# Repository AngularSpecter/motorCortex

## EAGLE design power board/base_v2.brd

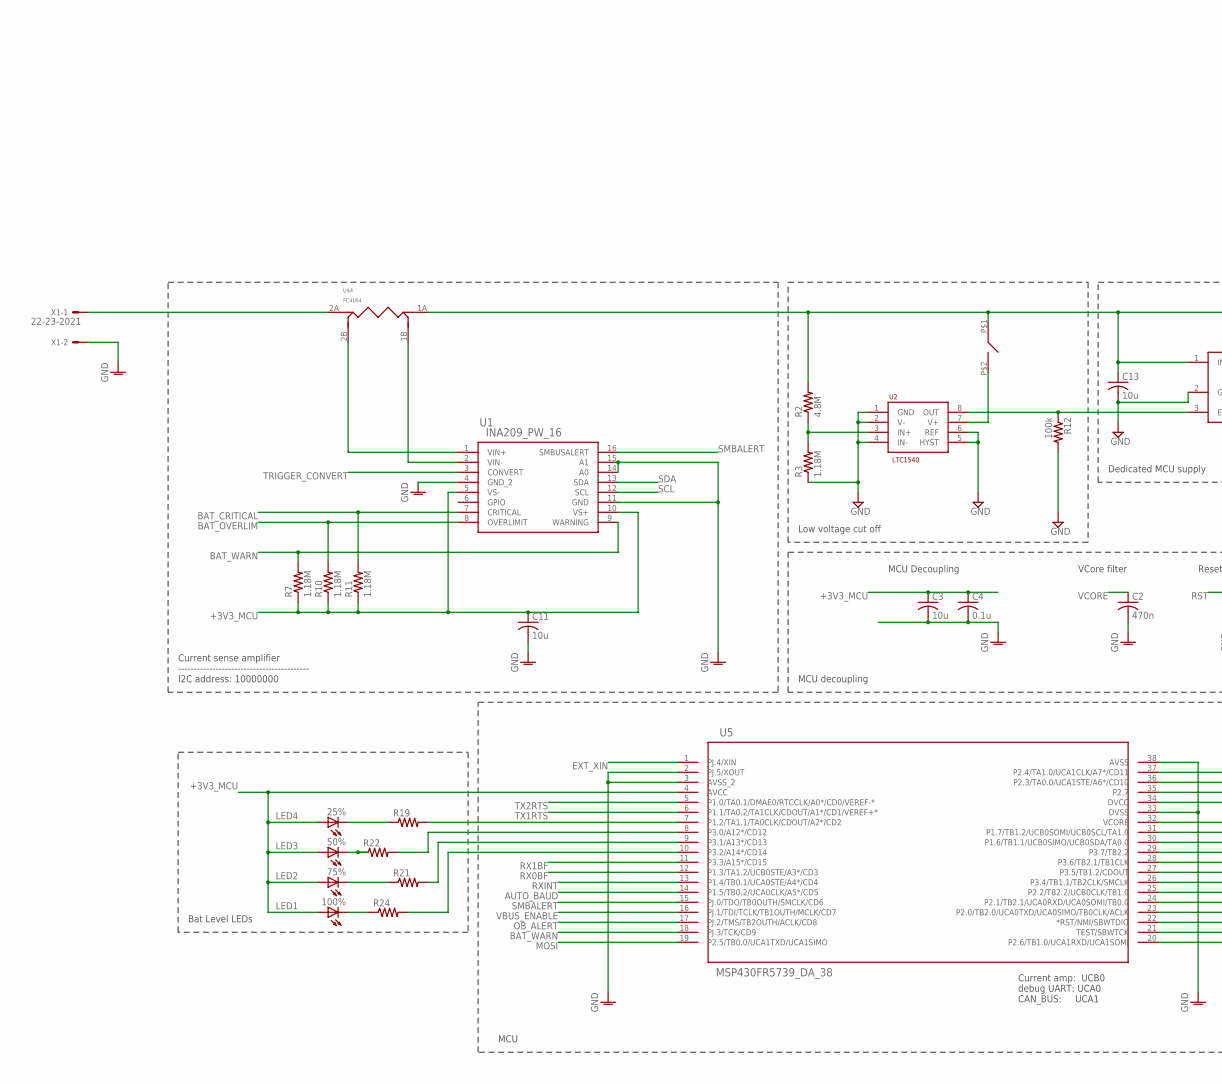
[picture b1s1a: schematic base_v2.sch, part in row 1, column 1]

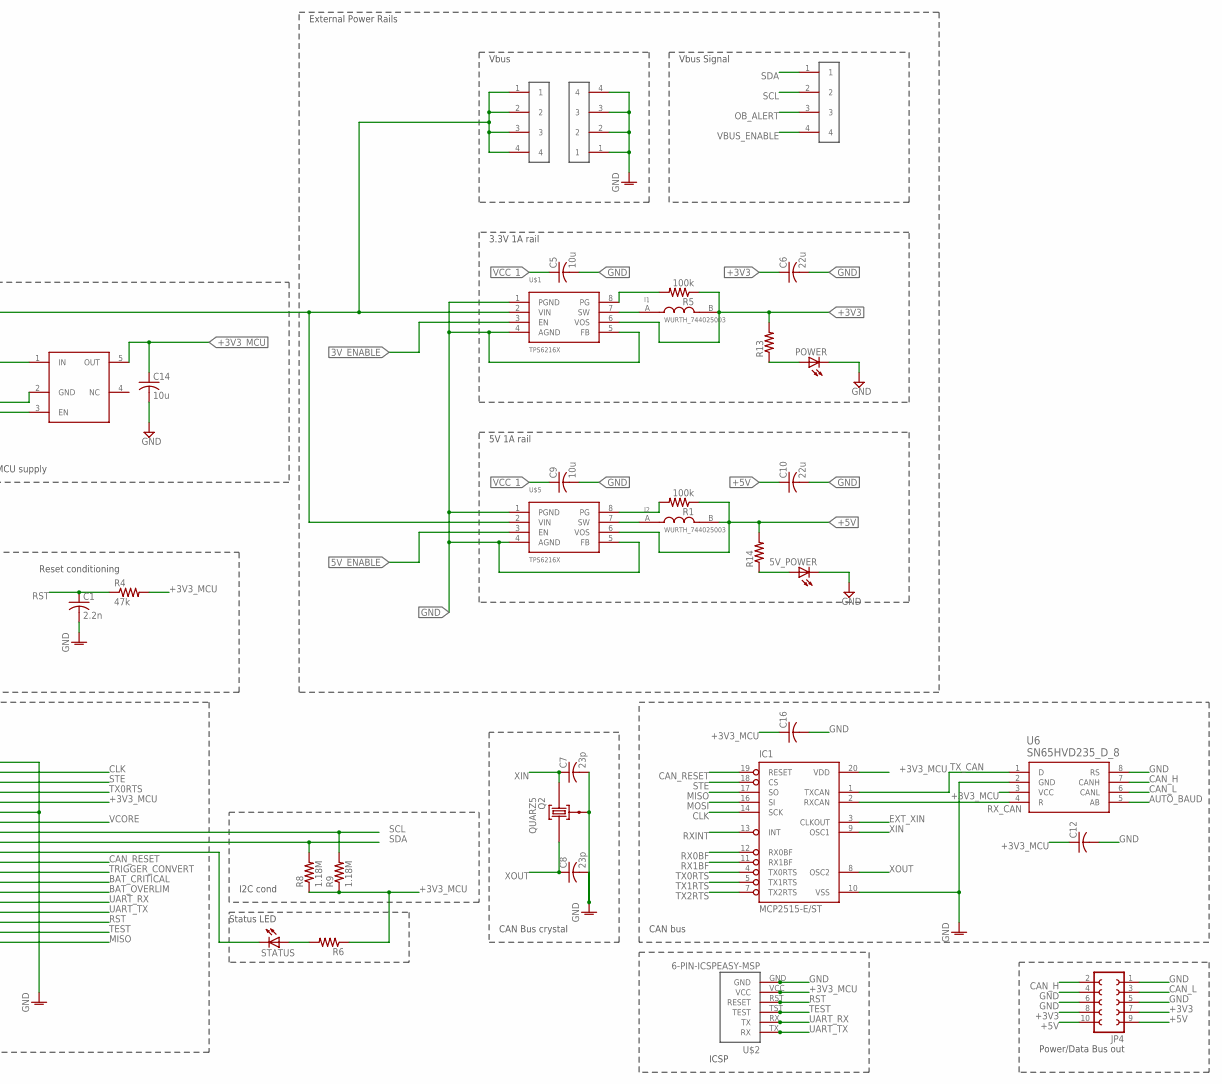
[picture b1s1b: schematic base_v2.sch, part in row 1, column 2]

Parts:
5V_POWER, 25%, 50%, 75%, 100%: LEDCHIP-LED0603; CHIP-LED0603
C1: 2.2n; C1206
C2: 470n; C1206
C3, C5, C9, C11, C13, C14: 10u; C1206
C4: 0.1u; C1206
C6, C10: 22u; C1206
C7, C8: 23p; C1206
C12, C16: C-USC0603; C0603
I1, I2: WURTH_744025003; INDUCTOR
IC1: MCP2515-E/ST; TSSOP20
JP4: FE05-2
POWER: LEDCHIP-LED0603; CHIP-LED0603
Q2: QUARZ5
R1, R5, R12: 100k; R1206
R2: 4.8M; R1206
R3: 1.18M; R1206
R4: 47k; R1206
R6, R13, R14, R19, R21, R22, R24: R-US_R0603; R0603
R7, R8, R9, R10, R11: 1.18M; R0805
STATUS: LEDCHIP-LED0603; CHIP-LED0603
U1: INA209_PW_16; PW16
U2: LTC1540; S8
U5: MSP430FR5739_DA_38; DA38
U6: SN65HVD235_D_8; D8
U$1, U$5: TPS6216X; DGK-8(VSSOP)
U$2: 6-PIN-ICSPEASY-MSP; EASYMSP-6PIN
U$3, U$8, U$11: 1X4_HEADER; 1X4-.1HEADER
U$4: FC4L64
U$6: TPS70930-Q1; SOT-23
U$7: A6SN; DIP1-SMT
X1: 22-23-2021

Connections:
3V_ENABLE: U$1.3 (EN)
5V_ENABLE: U$5.3 (EN)
+3V3: C6.1, I1.B, JP4.7, JP4.8, R5.1, R13.2, U$1.6 (VOS)
+3V3_MCU: 25%.A, 50%.A, 75%.A, 100%.A, C3.1, C4.1, C11.1, C12.1, C14.1, C16.1, IC1.20 (VDD), R4.2, R6.1, R7.1, R8.1, R9.1, R10.1, R11.1, U1.5 (VS-), U1.10 (VS+), U5.4 (AVCC), U5.34 (DVCC), U6.3 (VCC), U$2.VCC, U$6.5 (OUT)
+5V: C10.1, I2.B, JP4.9, JP4.10, R1.1, R14.2, U$5.6 (VOS)
AUTO_BAUD: U5.14 (P1.5/TB0.2/UCA0CLK/A5*/CD5), U6.5 (AB)
BAT_CRITICAL: R11.2, U1.7 (CRITICAL), U5.26 (P3.4/TB1.1/TB2CLK/SMCLK)
BAT_OVERLIM: R10.2, U1.8 (OVERLIMIT), U5.25 (P2.2/TB2.2/UCB0CLK/TB1.0)
BAT_WARN: R7.2, U1.9 (WARNING), U5.18 (PJ.3/TCK/CD9)
CAN_H: JP4.2, U6.7 (CANH)
CAN_L: JP4.3, U6.6 (CANL)
CAN_RESET: IC1.19 (RESET), U5.28 (P3.6/TB2.1/TB1CLK)
CLK: IC1.14 (SCK), U5.37 (P2.4/TA1.0/UCA1CLK/A7*/CD11)
EXT_XIN: IC1.3 (CLKOUT), U5.1 (PJ.4/XIN)
GND: 5V_POWER.C, C1.2, C2.2, C3.2, C4.2, C5.2, C6.2, C7.2, C8.2, C9.2, C10.2, C11.2, C12.2, C13.2, C14.2, C16.2, IC1.10 (VSS), JP4.1, JP4.4, JP4.5, JP4.6, POWER.C, Q2.GND@0 (0), R3.1, R12.2, U1.4 (GND_2), U1.11 (GND), U1.14 (A0), U1.15 (A1), U2.1 (GND), U2.2 (V-), U2.4 (IN-), U2.5 (HYST), U2.6 (REF), U5.2 (PJ.5/XOUT), U5.3 (AVSS_2), U5.33 (DVSS), U5.38 (AVSS), U6.2 (GND), U6.8 (RS), U$1.1 (PGND), U$1.4 (AGND), U$1.5 (FB), U$2.GND, U$3.1, U$3.2, U$3.3, U$3.4, U$5.1 (PGND), U$5.4 (AGND), U$5.5 (FB), U$6.2 (GND), X1.2
LED1: R24.2, U5.10 (P3.2/A14*/CD14)
LED2: R21.2, U5.9 (P3.1/A13*/CD13)
LED3: R22.2, U5.8 (P3.0/A12*/CD12)
LED4: R19.2, U5.7 (P1.2/TA1.1/TA0CLK/CDOUT/A2*/CD2)
MISO: IC1.17 (SO), U5.20 (P2.6/TB1.0/UCA1RXD/UCA1SOMI)
MOSI: IC1.16 (SI), U5.19 (P2.5/TB0.0/UCA1TXD/UCA1SIMO)
unnamed: 25%.C, R19.1
unnamed: U2.7 (V+), U$7.P$2 (2)
unnamed: R2.1, R3.2, U2.3 (IN+)
unnamed: I1.A, U$1.7 (SW)
unnamed: I2.A, U$5.7 (SW)
unnamed: R5.2, U$1.8 (PG)
unnamed: R1.2, U$5.8 (PG)
unnamed: U$4.2A (1A), X1.1
unnamed: POWER.A, R13.1
unnamed: 5V_POWER.A, R14.1
unnamed: U1.1 (VIN+), U$4.2B (1B)
unnamed: U1.2 (VIN-), U$4.1B (2B)
unnamed: R6.2, STATUS.A
unnamed: 50%.C, R22.1
unnamed: 75%.C, R21.1
unnamed: 100%.C, R24.1
NC: STATUS.C, U5.29 (P3.7/TB2.2)
OB_ALERT: U5.17 (PJ.2/TMS/TB2OUTH/ACLK/CD8), U$8.3
RST: C1.1, R4.1, U5.22 (*RST/NMI/SBWTDIO), U$2.RST (RESET)
RX0BF: IC1.12 (RX0BF), U5.12 (P1.3/TA1.2/UCB0STE/A3*/CD3)
RX1BF: IC1.11 (RX1BF), U5.11 (P3.3/A15*/CD15)
RXINT: IC1.13 (INT), U5.13 (P1.4/TB0.1/UCA0STE/A4*/CD4)
RX_CAN: IC1.2 (RXCAN), U6.4 (R)
SCL: R9.2, U1.12 (SCL), U5.31 (P1.7/TB1.2/UCB0SOMI/UCB0SCL/TA1.0), U$8.2
SDA: R8.2, U1.13 (SDA), U5.30 (P1.6/TB1.1/UCB0SIMO/UCB0SDA/TA0.0), U$8.1
SMBALERT: U1.16 (SMBUSALERT), U5.15 (PJ.0/TDO/TB0OUTH/SMCLK/CD6)
STE: IC1.18 (CS), U5.36 (P2.3/TA0.0/UCA1STE/A6*/CD10)
TEST: U5.21 (TEST/SBWTCK), U$2.TST (TEST)
TRIGGER_CONVERT: U1.3 (CONVERT), U5.27 (P3.5/TB1.2/CDOUT)
TX0RTS: IC1.4 (TX0RTS), U5.35 (P2.7)
TX1RTS: IC1.5 (TX1RTS), U5.6 (P1.1/TA0.2/TA1CLK/CDOUT/A1*/CD1/VEREF+*)
TX2RTS: IC1.7 (TX2RTS), U5.5 (P1.0/TA0.1/DMAE0/RTCCLK/A0*/CD0/VEREF-*)
TX_CAN: IC1.1 (TXCAN), U6.1 (D)
UART_RX: U5.24 (P2.1/TB2.1/UCA0RXD/UCA0SOMI/TB0.0), U$2.RX (TX)
UART_TX: U5.23 (P2.0/TB2.0/UCA0TXD/UCA0SIMO/TB0CLK/ACLK), U$2.TX (RX)
VBUS_ENABLE: U5.16 (PJ.1/TDI/TCLK/TB1OUTH/MCLK/CD7), U$8.4
VCC_1: C5.1, C9.1, C13.1, R2.2, U$1.2 (VIN), U$4.1A (2A), U$5.2 (VIN), U$6.1 (IN), U$7.P$1 (1), U$11.1, U$11.2, U$11.3, U$11.4
VCORE: C2.1, U5.32 (VCORE)
VENABLE: R12.1, U2.8 (OUT), U$6.3 (EN)
XIN: C7.1, IC1.9 (OSC1), Q2.2
XOUT: C8.1, IC1.8 (OSC2), Q2.1

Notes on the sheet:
MCU Decoupling
Reset conditioning
VCore filter
Current amp: UCB0 debug UART: UCA0 CAN_BUS: UCA1
3.3V 1A rail
5V 1A rail
Vbus
Current sense amplifier ------------------------------------------ I2C address: 10000000
Low voltage cut off
Dedicated MCU supply
Vbus Signal
External Power Rails
Bat Level LEDs
MCU decoupling
MCU
I2C cond
Status LED
CAN bus
CAN Bus crystal
ICSP
Power/Data Bus out

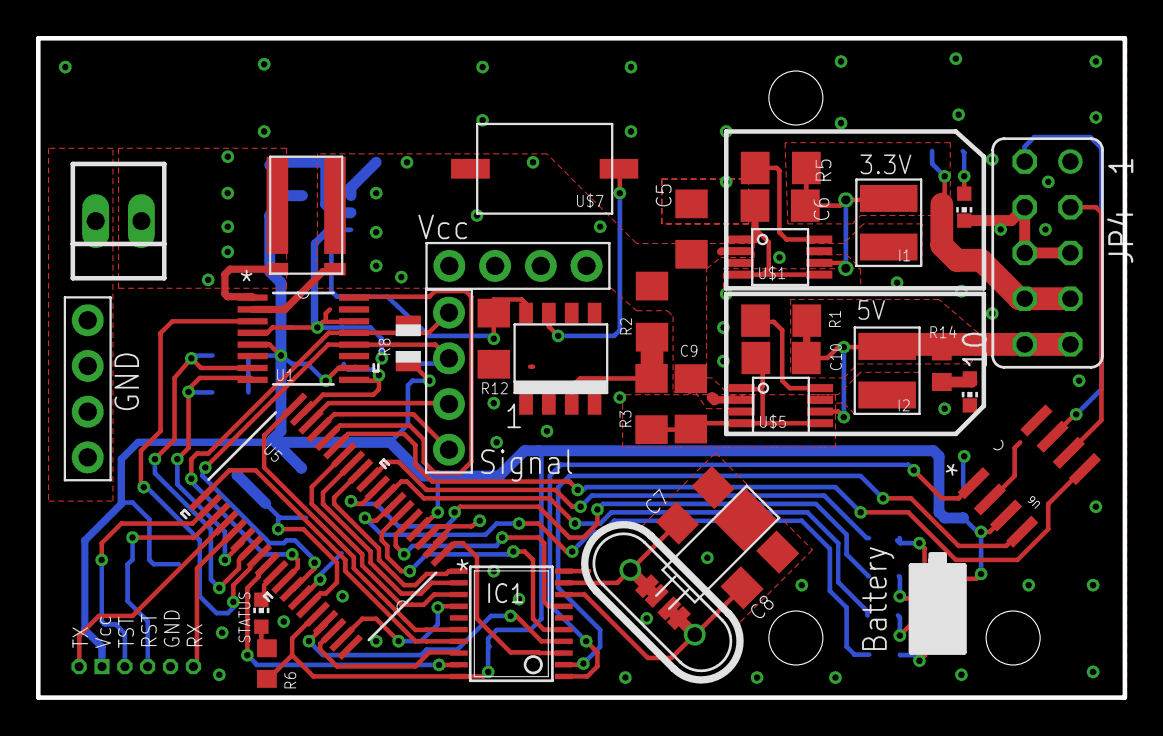
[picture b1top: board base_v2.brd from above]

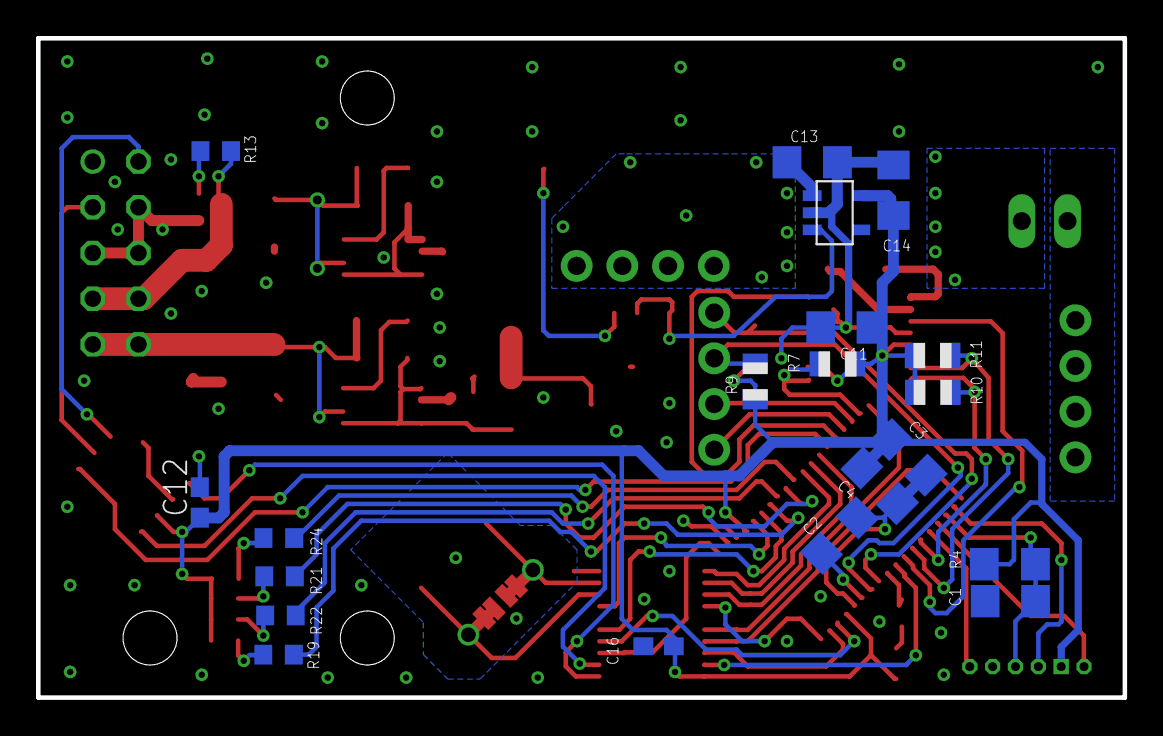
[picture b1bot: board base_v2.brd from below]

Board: 2 copper layers, 60.4 x 36.6 mm, 59 parts (20 on the bottom side), 60 nets.

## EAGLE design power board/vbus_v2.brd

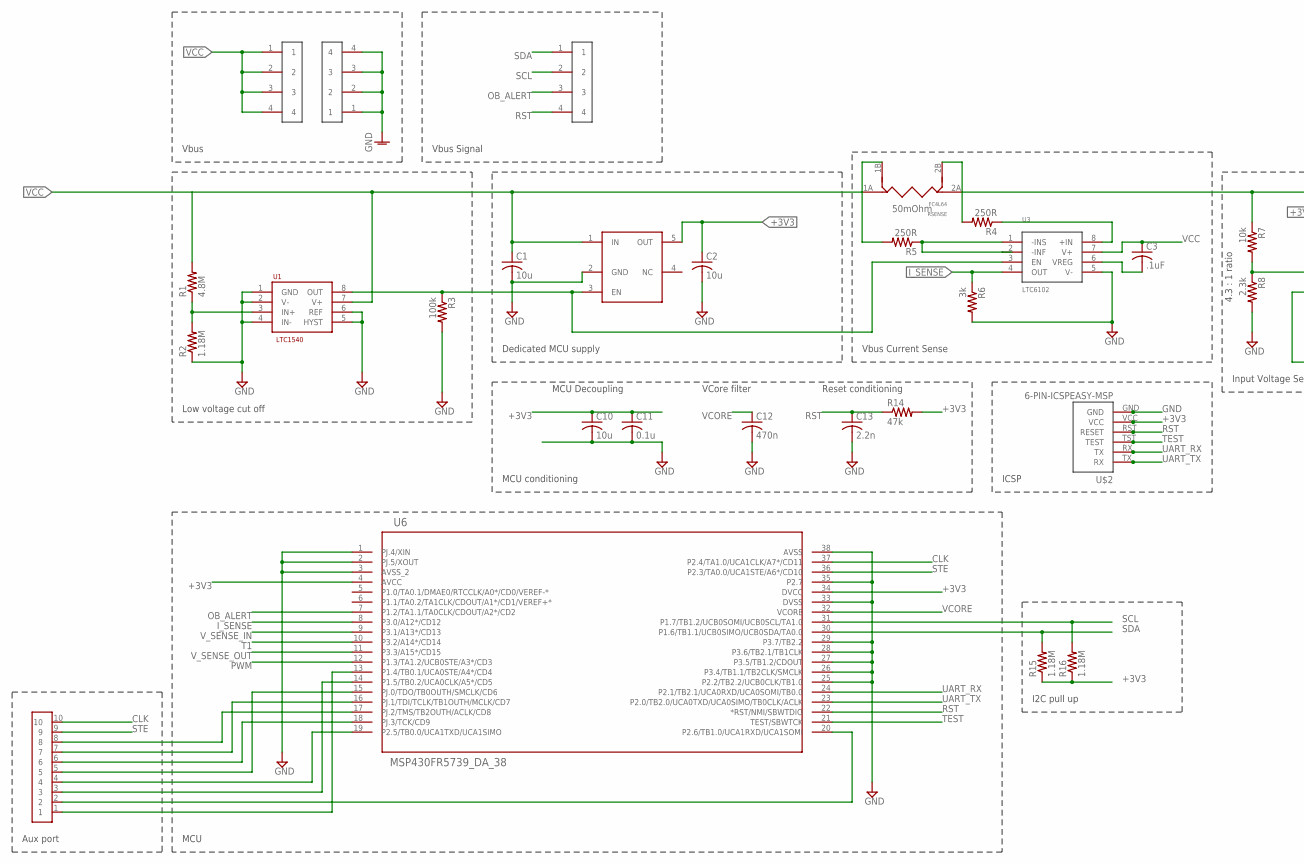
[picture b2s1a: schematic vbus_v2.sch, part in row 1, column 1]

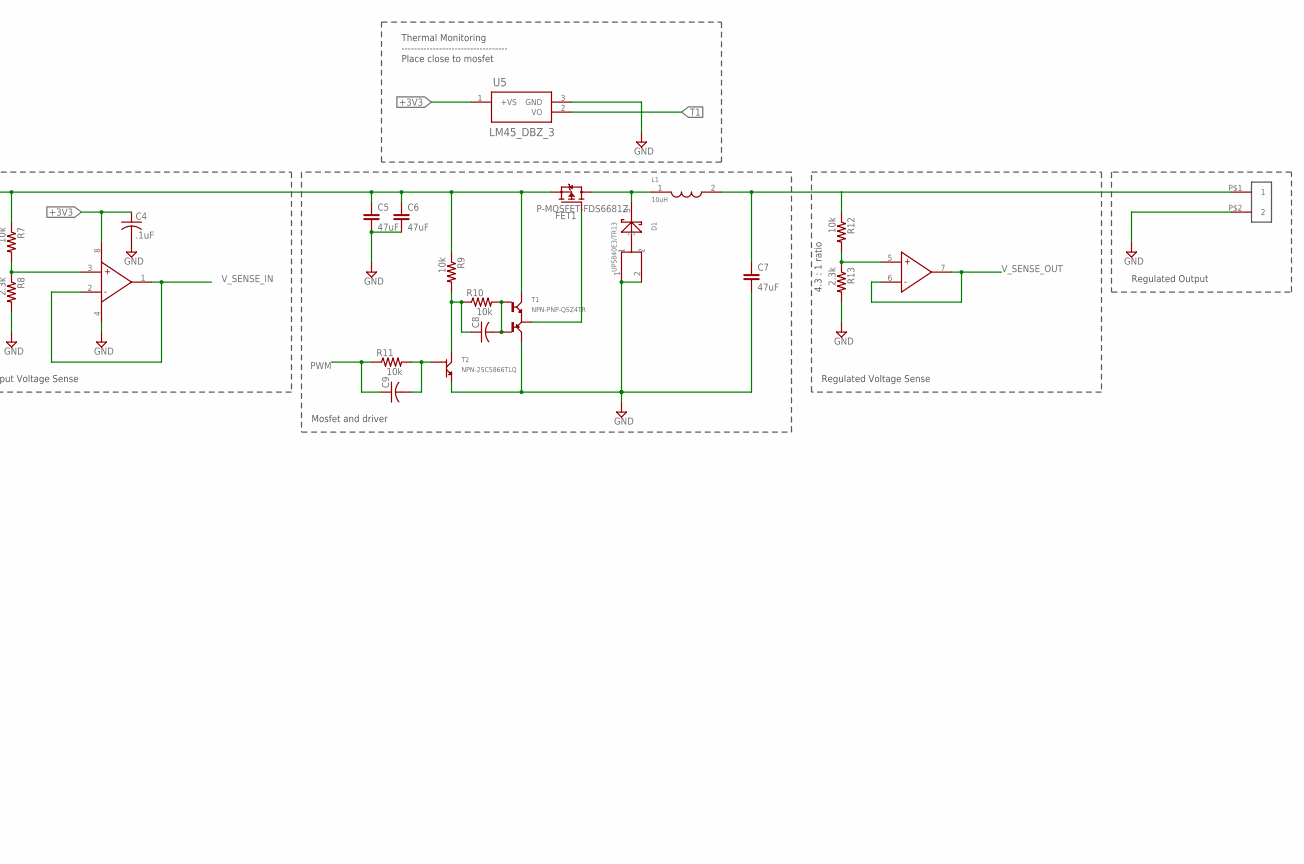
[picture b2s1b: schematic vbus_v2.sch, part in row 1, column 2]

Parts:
C1, C2, C10: 10u; C1206
C3, C4: .1uF; C0805
C5, C6, C7: 47uF; C1206
C8, C9: C-USC0805; C0805
C11: 0.1u; C1206
C12: 470n; C1206
C13: 2.2n; C1206
D1: UPS840E3/TR13; UPS840E3
FET1: P-MOSFET-FDS6681Z; SOIC-8
L1: 10uH; HCF1007
R1: 4.8M; R1206
R2: 1.18M; R1206
R3: 100k; R1206
R4, R5: 250R; M0805
R6: 3k; M0805
R7, R9, R10, R11, R12: 10k; M0805
R8, R13: 2.3k; M0805
R14: 47k; R1206
R15, R16: 1.18M; R0805
RSENSE: FC4L64
T1: NPN-PNP-QSZ4TR; TSMT5
T2: NPN-2SC5866TLQ; TSMT3
U1: LTC1540; S8
U2: TPS70930-Q1; SOT-23
U3: LTC6102; MS8
U4: LMP2202; D8-L
U5: LM45_DBZ_3; MF03A
U6: MSP430FR5739_DA_38; DA38
U$1: MICROPITCH; 2X5-1.27MM
U$2: 6-PIN-ICSPEASY-MSP; EASYMSP-6PIN
U$3, U$8, U$11: 1X4_HEADER; 1X4-.1HEADER
U$5: MOLEX-0436500200; MOLEX_MICROFIT-2

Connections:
+3V3: C2.1, C4.1, C10.1, C11.1, R14.2, R15.1, R16.1, U2.5 (OUT), U4.8 (VIN), U5.1 (+VS), U6.4 (AVCC), U6.34 (DVCC), U$2.VCC
CLK: U6.37 (P2.4/TA1.0/UCA1CLK/A7*/CD11), U$1.10
GND: C1.2, C2.2, C4.2, C5.2, C6.2, C7.2, C10.2, C11.2, C12.2, C13.2, D1.1, D1.2, R2.1, R3.2, R6.2, R8.2, R13.2, T1.5 (E), T2.2 (E), U1.1 (GND), U1.2 (V-), U1.4 (IN-), U1.5 (HYST), U1.6 (REF), U2.2 (GND), U3.5 (V-), U4.4 (GND), U5.3 (GND), U6.1 (PJ.4/XIN), U6.2 (PJ.5/XOUT), U6.3 (AVSS_2), U6.25 (P2.2/TB2.2/UCB0CLK/TB1.0), U6.26 (P3.4/TB1.1/TB2CLK/SMCLK), U6.27 (P3.5/TB1.2/CDOUT), U6.28 (P3.6/TB2.1/TB1CLK), U6.29 (P3.7/TB2.2), U6.33 (DVSS), U6.35 (P2.7), U6.38 (AVSS), U$2.GND, U$3.1, U$3.2, U$3.3, U$3.4, U$5.P$2 (2)
I_SENSE: R6.1, U3.4 (OUT), U6.8 (P3.0/A12*/CD12)
unnamed: R5.2, RSENSE.1B (2B)
unnamed: R1.1, R2.2, U1.3 (IN+)
unnamed: R4.1, U3.8 (+IN)
unnamed: R5.1, U3.1 (-INS), U3.2 (-INF)
unnamed: R4.2, RSENSE.2B (1B)
unnamed: C8.2, R10.2, T1.1 (G2), T1.3 (G1)
unnamed: C3.2, U3.6 (VREG)
unnamed: D1.3, FET1.1 (S), FET1.2 (S), FET1.3 (S), L1.1 (A)
unnamed: C8.1, R9.2, R10.1, T2.3 (C)
unnamed: C9.2, R11.2, T2.1 (B)
unnamed: U6.19 (P2.5/TB0.0/UCA1TXD/UCA1SIMO), U$1.4
unnamed: FET1.4 (G), T1.2 (G)
unnamed: U6.17 (PJ.2/TMS/TB2OUTH/ACLK/CD8), U$1.8
unnamed: U6.16 (PJ.1/TDI/TCLK/TB1OUTH/MCLK/CD7), U$1.7
unnamed: C5.1, C6.1, FET1.5 (D), FET1.6 (D), FET1.7 (D), FET1.8 (D), R7.1, R9.1, RSENSE.2A (1A), T1.4 (C)
unnamed: U6.15 (PJ.0/TDO/TB0OUTH/SMCLK/CD6), U$1.5
unnamed: U6.14 (P1.5/TB0.2/UCA0CLK/A5*/CD5), U$1.3
unnamed: U6.13 (P1.4/TB0.1/UCA0STE/A4*/CD4), U$1.1
unnamed: U6.18 (PJ.3/TCK/CD9), U$1.6
unnamed: U6.20 (P2.6/TB1.0/UCA1RXD/UCA1SOMI), U$1.2
OB_ALERT: U6.7 (P1.2/TA1.1/TA0CLK/CDOUT/A2*/CD2), U$8.3
PWM: C9.1, R11.1, U6.12 (P1.3/TA1.2/UCB0STE/A3*/CD3)
RST: C13.1, R14.1, U6.22 (*RST/NMI/SBWTDIO), U$2.RST (RESET), U$8.4
SCL: R16.2, U6.31 (P1.7/TB1.2/UCB0SOMI/UCB0SCL/TA1.0), U$8.2
SDA: R15.2, U6.30 (P1.6/TB1.1/UCB0SIMO/UCB0SDA/TA0.0), U$8.1
STE: U6.36 (P2.3/TA0.0/UCA1STE/A6*/CD10), U$1.9
T1: U5.2 (VO), U6.10 (P3.2/A14*/CD14)
TEST: U6.21 (TEST/SBWTCK), U$2.TST (TEST)
UART_RX: U6.24 (P2.1/TB2.1/UCA0RXD/UCA0SOMI/TB0.0), U$2.RX (TX)
UART_TX: U6.23 (P2.0/TB2.0/UCA0TXD/UCA0SIMO/TB0CLK/ACLK), U$2.TX (RX)
VCC: C1.1, C3.1, R1.2, RSENSE.1A (2A), U1.7 (V+), U2.1 (IN), U3.7 (V+), U$11.1, U$11.2, U$11.3, U$11.4
VCORE: C12.1, U6.32 (VCORE)
VENABLE: R3.1, U1.8 (OUT), U2.3 (EN), U3.3 (EN)
V_OUT: C7.1, L1.2 (B), R12.1, U$5.P$1 (1)
V_SENSE: R12.2, R13.1, U4.5 (+)
V_SENSE_IN: U4.1 (OUT), U4.2 (-), U6.9 (P3.1/A13*/CD13)
V_SENSE_IN_P: R7.2, R8.1, U4.3 (+)
V_SENSE_OUT: U4.6 (-), U4.7 (OUT), U6.11 (P3.3/A15*/CD15)

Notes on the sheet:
MCU Decoupling
Reset conditioning
VCore filter
Vbus
Low voltage cut off
Dedicated MCU supply
Vbus Signal
Thermal Monitoring ---------------------------------- Place close to mosfet
Regulated Voltage Sense
4.3 : 1 ratio
Vbus Current Sense
50mOhm
Input Voltage Sense
Mosfet and driver
Aux port
ICSP
MCU conditioning
I2C pull up
MCU
Regulated Output

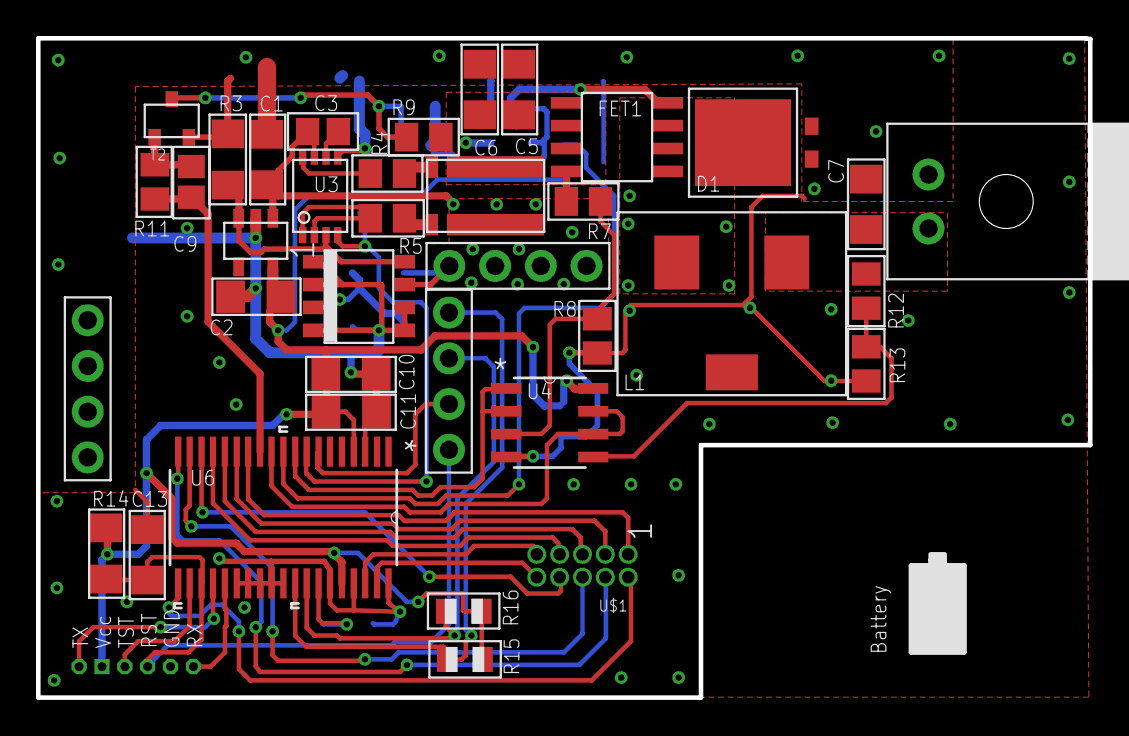
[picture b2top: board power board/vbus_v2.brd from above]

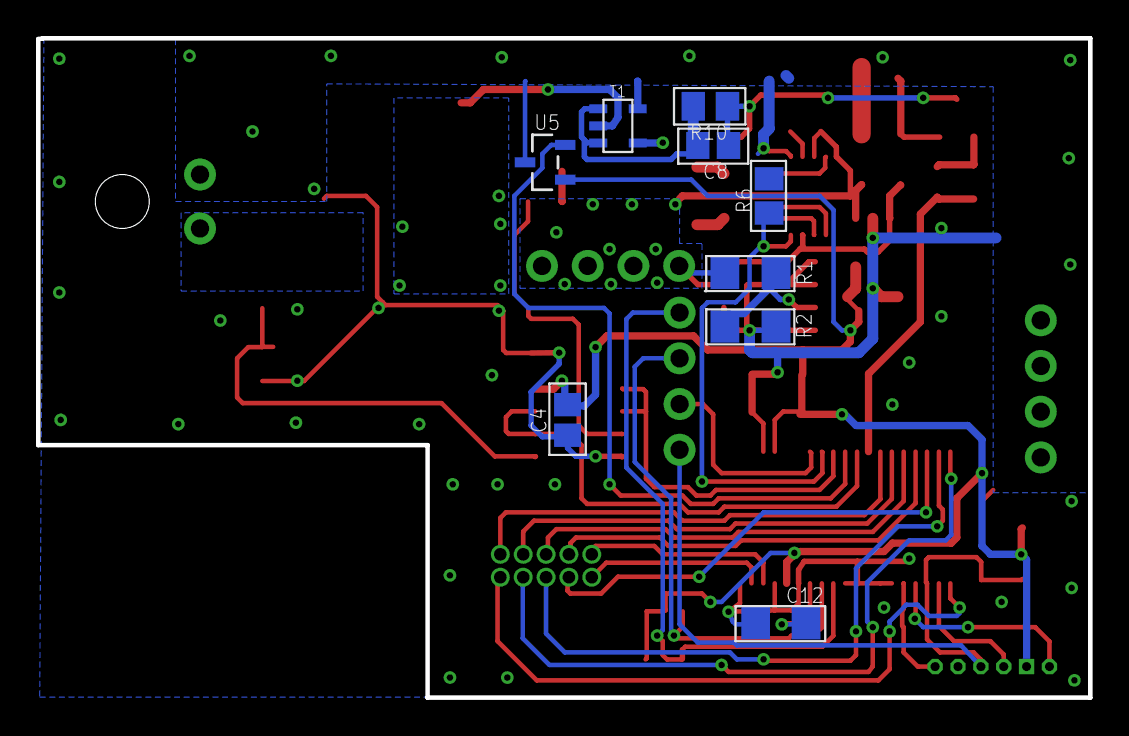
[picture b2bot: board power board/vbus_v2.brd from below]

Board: 2 copper layers, 58.4 x 36.6 mm, 47 parts (9 on the bottom side), 42 nets.

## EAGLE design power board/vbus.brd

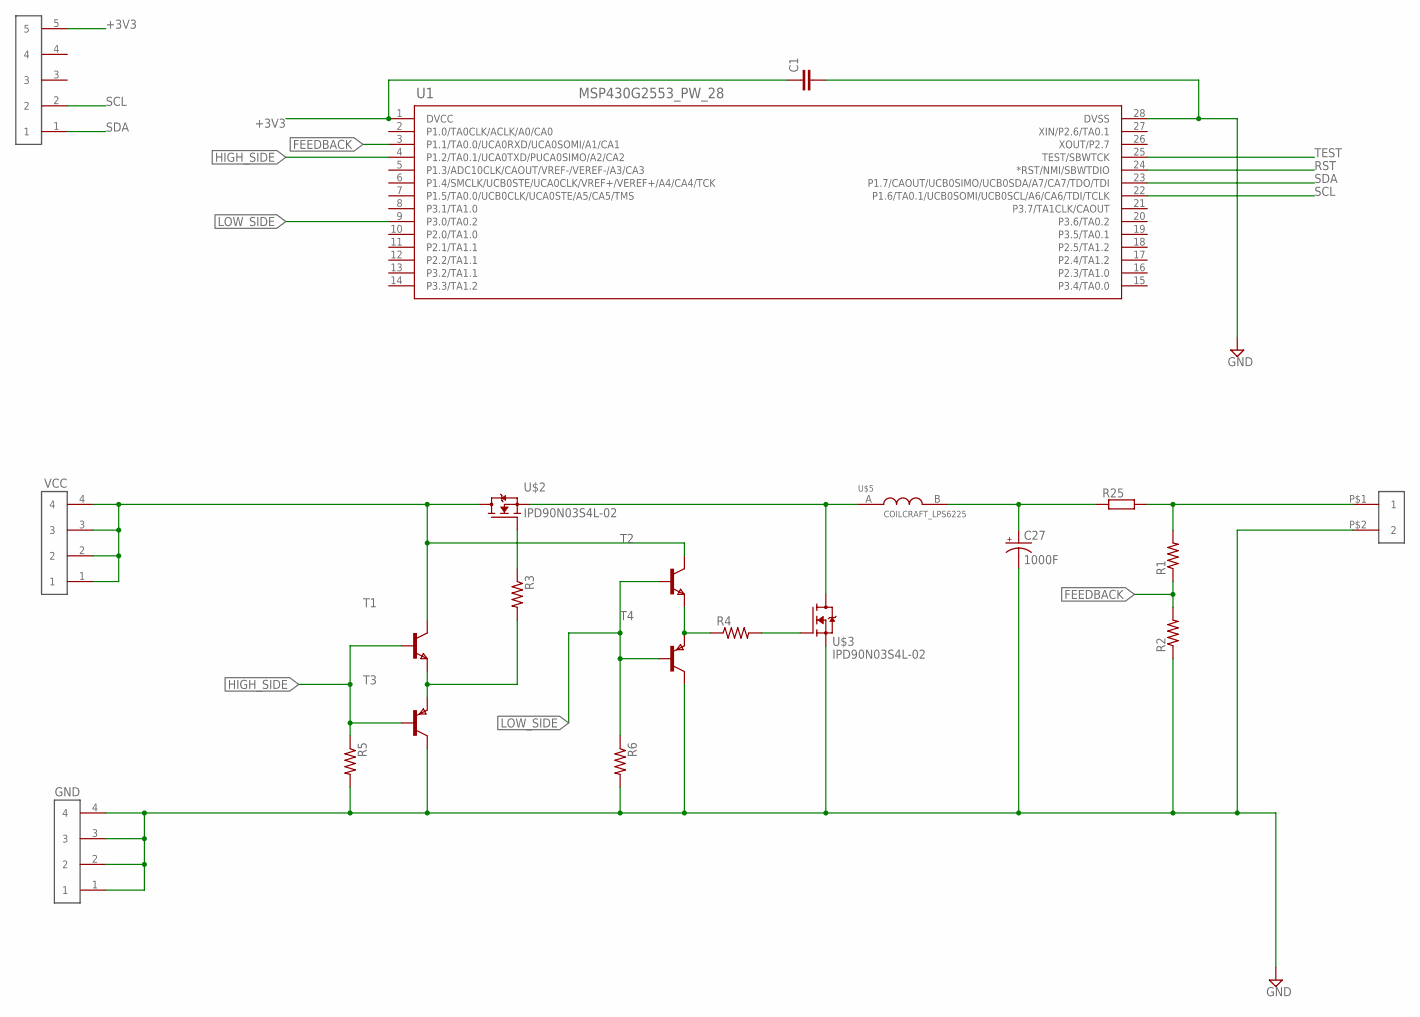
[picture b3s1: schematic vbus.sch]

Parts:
C1: C-EUC0603; C0603
C27: 1000F; TAP5-60
R1, R2, R3, R4, R5, R6: R-US_R1206; R1206
R25: SMR
T1, T2: NPNSOT23-6; SOT23-6
T3, T4: PNPSOT23-6; SOT23-6
U1: MSP430G2553_PW_28; PW28
U$2, U$3: IPD90N03S4L-02; P/PG-TO252-3-11
U$4: 1X5_HEADER; 1X5-.1HEADER
U$5: COILCRAFT_LPS6225; INDUCTOR
U$11, U$12: 1X4_HEADER; 1X4-.1HEADER
VBUS: MOLEX-0436500200; MOLEX_MICROFIT-2

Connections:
+3V3: C1.1, U1.1 (DVCC), U$4.5
FEEDBACK: R1.1, R2.2, U1.3 (P1.1/TA0.0/UCA0RXD/UCA0SOMI/A1/CA1)
GND: C1.2, C27.-, R2.1, R5.2, R6.2, T3.1 (C), T3.2 (C), T3.5 (C), T3.6 (C), T4.1 (C), T4.2 (C), T4.5 (C), T4.6 (C), U1.28 (DVSS), U$3.3 (S), U$12.1, U$12.2, U$12.3, U$12.4, VBUS.P$2 (2)
HIGH_SIDE: R5.1, T1.3 (B), T3.3 (B), U1.4 (P1.2/TA0.1/UCA0TXD/PUCA0SIMO/A2/CA2)
LOW_SIDE: R6.1, T2.3 (B), T4.3 (B), U1.9 (P3.0/TA0.2)
unnamed: R3.1, U$2.1 (G)
unnamed: U$2.3 (S), U$3.2 (D), U$5.A
unnamed: R1.2, R25.1, VBUS.P$1 (1)
unnamed: R3.2, T1.4 (E), T3.4 (E)
unnamed: R4.2, U$3.1 (G)
unnamed: R4.1, T2.4 (E), T4.4 (E)
RST: U1.24 (*RST/NMI/SBWTDIO)
SCL: U1.22 (P1.6/TA0.1/UCB0SOMI/UCB0SCL/A6/CA6/TDI/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), U$4.2
SDA: U1.23 (P1.7/CAOUT/UCB0SIMO/UCB0SDA/A7/CA7/TDO/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), U$4.1
TEST: U1.25 (TEST/SBWTCK)
VBUS: C27.+, R25.2, U$5.B
VCC: T1.1 (C), T1.2 (C), T1.5 (C), T1.6 (C), T2.1 (C), T2.2 (C), T2.5 (C), T2.6 (C), U$2.2 (D), U$11.1, U$11.2, U$11.3, U$11.4

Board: 2 copper layers, 21 parts (3 on the bottom side), 15 nets, no tracks yet.

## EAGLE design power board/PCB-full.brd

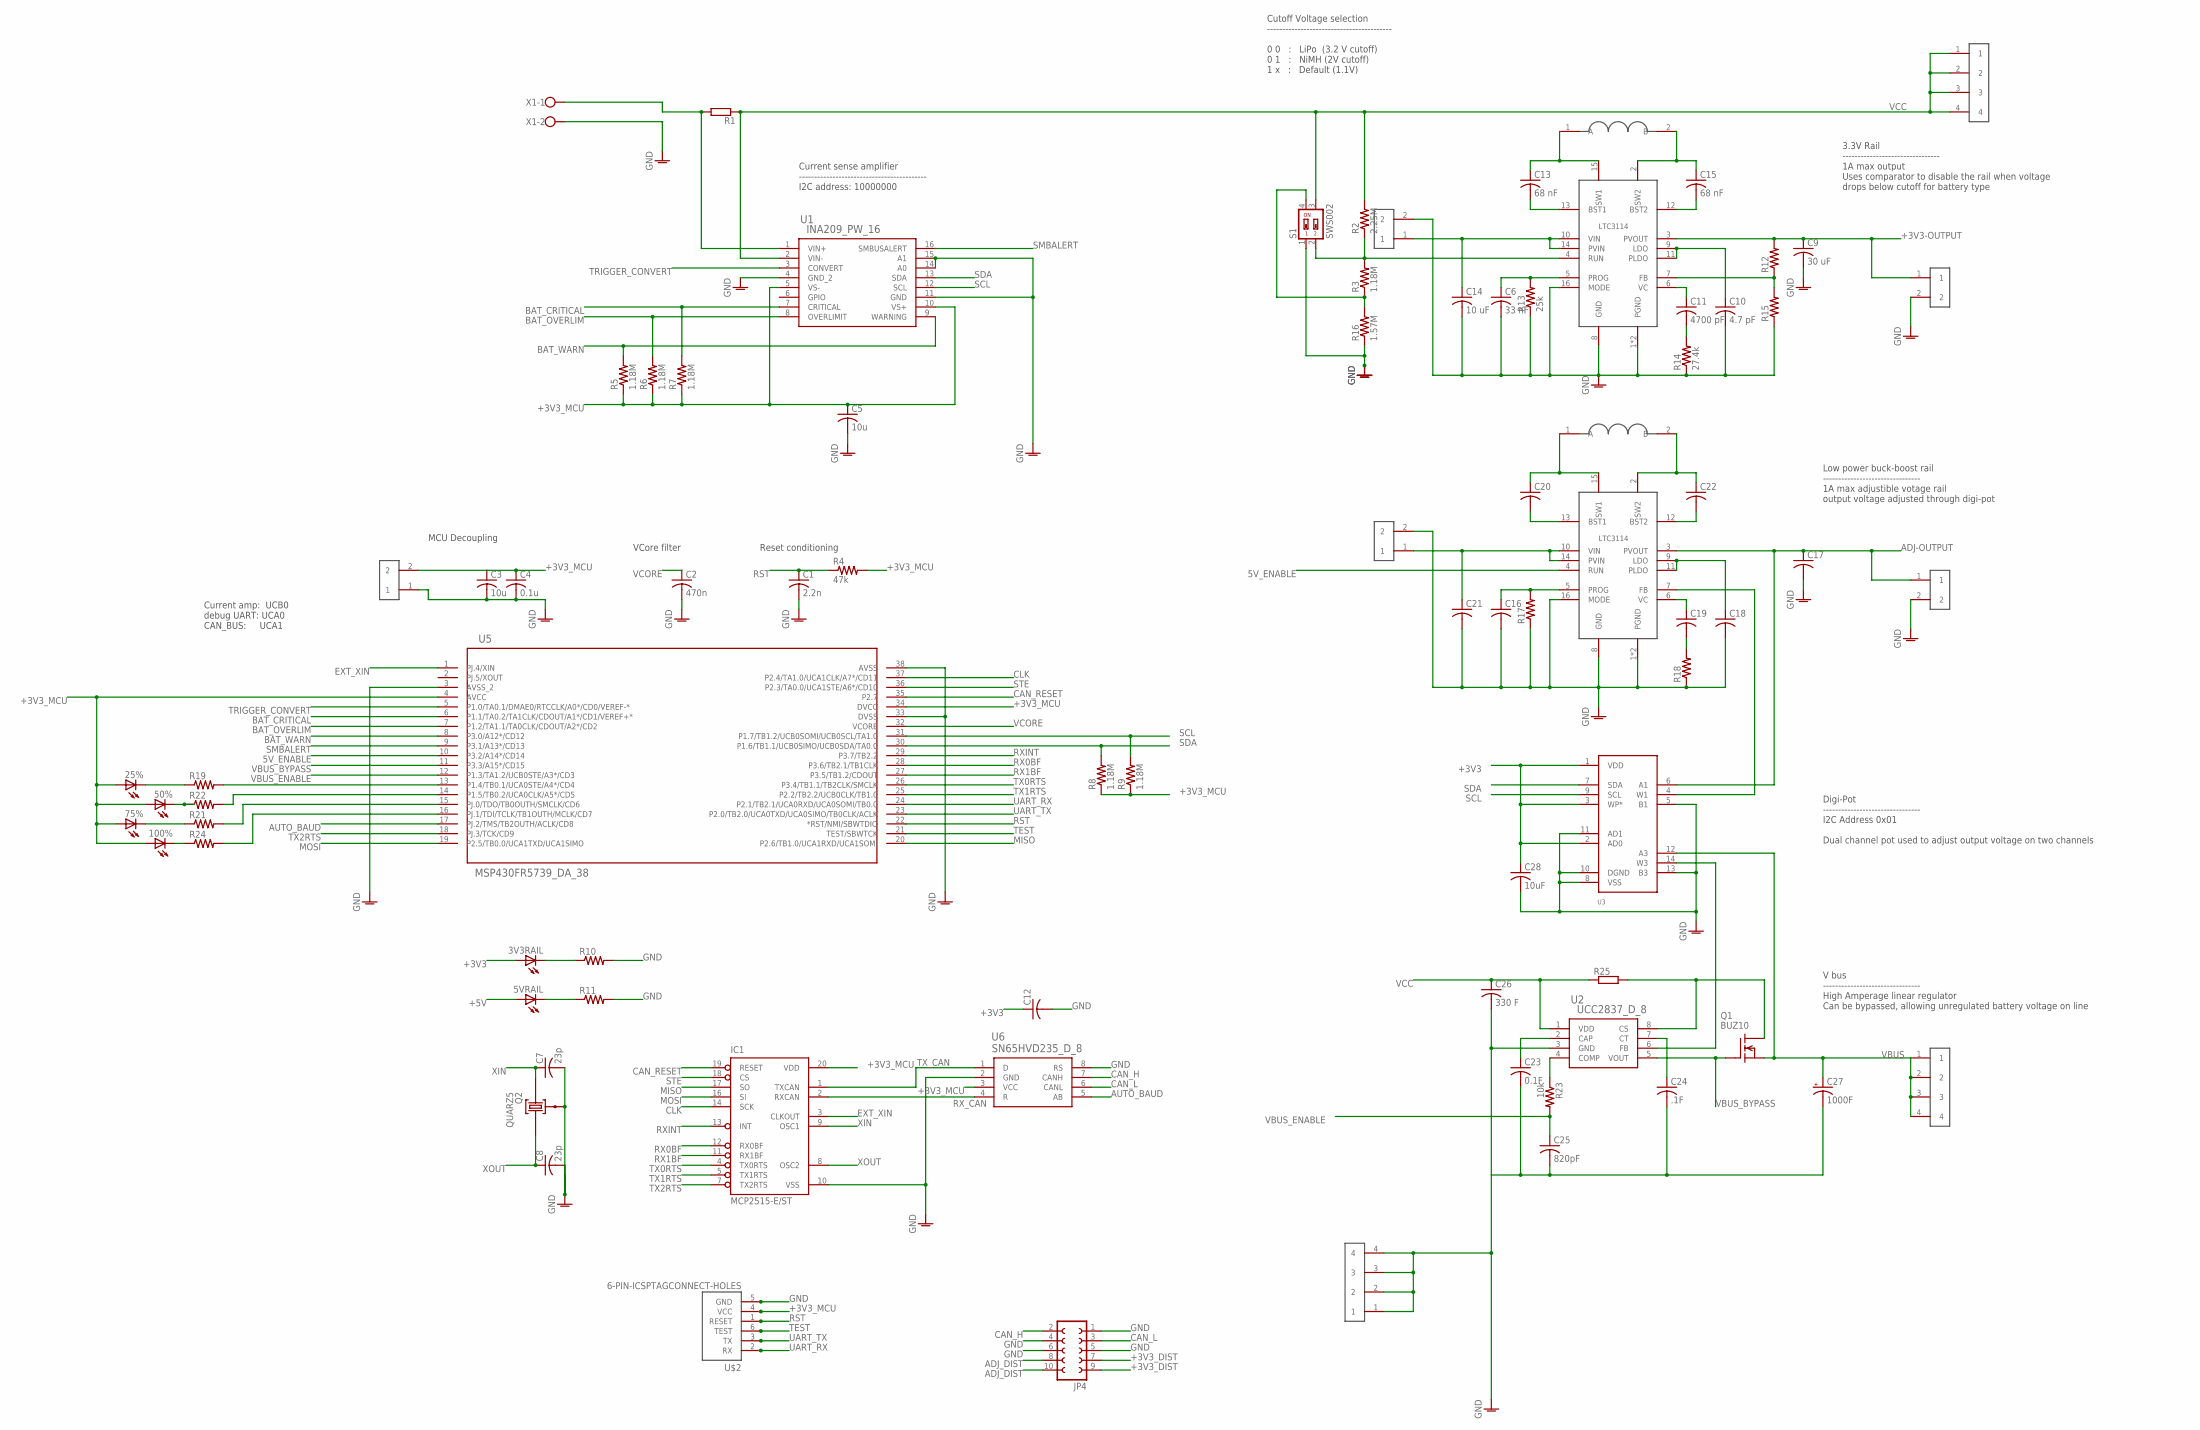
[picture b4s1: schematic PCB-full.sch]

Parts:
3V3RAIL, 5VRAIL, 25%, 50%, 75%, 100%: LEDCHIP-LED0603; CHIP-LED0603
C1: 2.2n; C1206
C2: 470n; C1206
C3, C5: 10u; C1206
C4: 0.1u; C1206
C6: 33 nF; C0805
C7, C8: 23p; C1206
C9: 30 uF; C0805
C10: 4.7 pF; C0805
C11: 4700 pF; C0805
C12: C-USC0603; C0603
C13, C15: 68 nF; C0805
C14: 10 uF; C0805
C16, C17, C18, C19, C20, C21, C22: C-USC0805; C0805
C23: 0.1F; C0805
C24: .1F; C0805
C25: 820pF; C0805
C26: 330 F; C0805
C27: 1000F; TAP5-60
C28: 10uF; C0603
IC1: MCP2515-E/ST; TSSOP20
JP4: FE05-2
Q1: BUZ10; TO220
Q2: QUARZ5
R1, R25: SMR
R2: 2.25M; R0805
R3, R5, R6, R7, R8, R9: 1.18M; R0805
R4: 47k; R1206
R10, R11, R19, R21, R22, R24: R-US_R0603; R0603
R12, R15, R17, R18: R-US_M0805; M0805
R13: 25k; M0805
R14: 27.4k; M0805
R16: 1.57M; R0805
R23: 10k; M0805
S1: SWS002; SMS-002
U1: INA209_PW_16; PW16
U2: UCC2837_D_8; D8
U3: AD5252BRU10; RU_14
U5: MSP430FR5739_DA_38; DA38
U6: SN65HVD235_D_8; D8
U$1, U$3: LTC3114; TSSOP-16
U$2: 6-PIN-ICSPTAGCONNECT-HOLES; TAGCONNECT-HOLES
U$4, U$5: DC630R-562M; DC630
U$6, U$7, U$8, U$9, U$10: 1X2_HEADER; 1X2-.1HEADER
U$11, U$12, U$14: 1X4_HEADER; 1X4-.1HEADER
X1: W237-102

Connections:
5V_ENABLE: U5.10 (P3.2/A14*/CD14), U$3.4 (RUN)
+3V3: 3V3RAIL.A, C12.1, C28.1, U3.1 (VDD), U3.2 (AD0), U3.3 (WP*)
+3V3-OUTPUT: C9.1, R12.2, U$1.3 (PVOUT), U$7.1
+3V3_DIST: JP4.7, JP4.9
+3V3_MCU: 25%.A, 50%.A, 75%.A, 100%.A, C3.1, C4.1, C5.1, IC1.20 (VDD), R4.2, R5.1, R6.1, R7.1, R8.1, R9.1, U1.5 (VS-), U1.10 (VS+), U5.4 (AVCC), U5.34 (DVCC), U6.3 (VCC), U$2.4 (VCC), U$6.2
+5V: 5VRAIL.A
ADJ-OUTPUT: C17.1, U3.6 (A1), U$3.3 (PVOUT), U$8.1
ADJ_DIST: JP4.8, JP4.10
AUTO_BAUD: U5.17 (PJ.2/TMS/TB2OUTH/ACLK/CD8), U6.5 (AB)
BAT_CRITICAL: R7.2, U1.7 (CRITICAL), U5.6 (P1.1/TA0.2/TA1CLK/CDOUT/A1*/CD1/VEREF+*)
BAT_OVERLIM: R6.2, U1.8 (OVERLIMIT), U5.7 (P1.2/TA1.1/TA0CLK/CDOUT/A2*/CD2)
BAT_WARN: R5.2, U1.9 (WARNING), U5.8 (P3.0/A12*/CD12)
CAN_H: JP4.2, U6.7 (CANH)
CAN_L: JP4.3, U6.6 (CANL)
CAN_RESET: IC1.19 (RESET), U5.35 (P2.7)
CLK: IC1.14 (SCK), U5.37 (P2.4/TA1.0/UCA1CLK/A7*/CD11)
EXT_XIN: IC1.3 (CLKOUT), U5.1 (PJ.4/XIN)
GND: C1.2, C2.2, C3.2, C4.2, C5.2, C6.2, C7.2, C8.2, C10.2, C12.2, C14.2, C16.2, C17.2, C18.2, C21.2, C23.2, C24.2, C25.2, C26.2, C27.-, C28.2, IC1.10 (VSS), JP4.1, JP4.4, JP4.5, JP4.6, Q2.GND@0 (0), R10.2, R11.2, R13.1, R14.1, R15.1, R16.1, R17.1, R18.1, S1.1, U1.4 (GND_2), U1.11 (GND), U1.14 (A0), U1.15 (A1), U2.3 (GND), U3.5 (B1), U3.8 (VSS), U3.10 (DGND), U3.11 (AD1), U3.13 (B3), U5.3 (AVSS_2), U5.33 (DVSS), U5.38 (AVSS), U6.2 (GND), U6.8 (RS), U$1.1 (PGND), U$1.8 (GND), U$1.16 (MODE), U$1.PAD (PGND), U$2.5 (GND), U$3.1 (PGND), U$3.8 (GND), U$3.16 (MODE), U$3.PAD (PGND), U$6.1, U$7.2, U$8.2, U$9.2, U$10.2, U$12.1, U$12.2, U$12.3, U$12.4, X1.2
GNDA: C9.2
MISO: IC1.17 (SO), U5.20 (P2.6/TB1.0/UCA1RXD/UCA1SOMI)
MOSI: IC1.16 (SI), U5.19 (P2.5/TB0.0/UCA1TXD/UCA1SIMO)
unnamed: 25%.C, R19.1
unnamed: R3.1, R16.2, S1.4
unnamed: R19.2, U5.13 (P1.4/TB0.1/UCA0STE/A4*/CD4)
unnamed: 5VRAIL.C, R11.1
unnamed: 3V3RAIL.C, R10.1
unnamed: C13.1, U$1.15 (SW1), U$4.1 (A)
unnamed: C15.1, U$1.2 (SW2), U$4.2 (B)
unnamed: C13.2, U$1.13 (BST1)
unnamed: C15.2, U$1.12 (BST2)
unnamed: C20.1, U$3.15 (SW1), U$5.1 (A)
unnamed: C6.1, R13.2, U$1.5 (PROG)
unnamed: C22.1, U$3.2 (SW2), U$5.2 (B)
unnamed: C10.1, U$1.9 (LDO), U$1.11 (PLDO)
unnamed: C20.2, U$3.13 (BST1)
unnamed: C11.1, U$1.6 (VC)
unnamed: C11.2, R14.2
unnamed: R12.1, R15.2, U$1.7 (FB)
unnamed: C22.2, U$3.12 (BST2)
unnamed: C16.1, R17.2, U$3.5 (PROG)
unnamed: C18.1, U$3.9 (LDO), U$3.11 (PLDO)
unnamed: R2.1, R3.2, S1.2, U$1.4 (RUN)
unnamed: C19.1, U$3.6 (VC)
unnamed: C19.2, R18.2
unnamed: U3.4 (W1), U$3.7 (FB)
unnamed: Q1.2 (D), R25.1, U2.8 (CS)
unnamed: R22.2, U5.14 (P1.5/TB0.2/UCA0CLK/A5*/CD5)
unnamed: C23.1, U2.2 (CAP)
unnamed: U2.6 (FB), U3.14 (W3)
unnamed: R23.1, U2.4 (COMP)
unnamed: R21.2, U5.15 (PJ.0/TDO/TB0OUTH/SMCLK/CD6)
unnamed: R24.2, U5.16 (PJ.1/TDI/TCLK/TB1OUTH/MCLK/CD7)
unnamed: C24.1, U2.7 (CT)
unnamed: 50%.C, R22.1
unnamed: 75%.C, R21.1
unnamed: 100%.C, R24.1
RST: C1.1, R4.1, U5.22 (*RST/NMI/SBWTDIO), U$2.1 (RESET)
RX0BF: IC1.12 (RX0BF), U5.28 (P3.6/TB2.1/TB1CLK)
RX1BF: IC1.11 (RX1BF), U5.27 (P3.5/TB1.2/CDOUT)
RXINT: IC1.13 (INT), U5.29 (P3.7/TB2.2)
RX_CAN: IC1.2 (RXCAN), U6.4 (R)
SCL: R9.2, U1.12 (SCL), U3.9 (SCL), U5.31 (P1.7/TB1.2/UCB0SOMI/UCB0SCL/TA1.0)
SDA: R8.2, U1.13 (SDA), U3.7 (SDA), U5.30 (P1.6/TB1.1/UCB0SIMO/UCB0SDA/TA0.0)
SMBALERT: U1.16 (SMBUSALERT), U5.9 (P3.1/A13*/CD13)
STE: IC1.18 (CS), U5.36 (P2.3/TA0.0/UCA1STE/A6*/CD10)
TEST: U5.21 (TEST/SBWTCK), U$2.6 (TEST)
TRIGGER_CONVERT: U1.3 (CONVERT), U5.5 (P1.0/TA0.1/DMAE0/RTCCLK/A0*/CD0/VEREF-*)
TX0RTS: IC1.4 (TX0RTS), U5.26 (P3.4/TB1.1/TB2CLK/SMCLK)
TX1RTS: IC1.5 (TX1RTS), U5.25 (P2.2/TB2.2/UCB0CLK/TB1.0)
TX2RTS: IC1.7 (TX2RTS), U5.18 (PJ.3/TCK/CD9)
TX_CAN: IC1.1 (TXCAN), U6.1 (D)
UART_RX: U5.24 (P2.1/TB2.1/UCA0RXD/UCA0SOMI/TB0.0), U$2.2 (RX)
UART_TX: U5.23 (P2.0/TB2.0/UCA0TXD/UCA0SIMO/TB0CLK/ACLK), U$2.3 (TX)
VBUS: C27.+, Q1.3 (S), U3.12 (A3), U$14.1, U$14.2, U$14.3, U$14.4
VBUS_BYPASS: Q1.1 (G), U2.5 (VOUT), U5.11 (P3.3/A15*/CD15)
VBUS_ENABLE: C25.1, R23.2, U5.12 (P1.3/TA1.2/UCB0STE/A3*/CD3)
VCC: C26.1, R1.2, R2.2, R25.2, S1.3, U1.2 (VIN-), U2.1 (VDD), U$11.1, U$11.2, U$11.3, U$11.4
VCC_1: R1.1, U1.1 (VIN+), X1.1
VCC_3V: C14.1, U$1.10 (VIN), U$1.14 (PVIN), U$9.1
VCC_ADJ: C21.1, U$3.10 (VIN), U$3.14 (PVIN), U$10.1
VCORE: C2.1, U5.32 (VCORE)
XIN: C7.1, IC1.9 (OSC1), Q2.2
XOUT: C8.1, IC1.8 (OSC2), Q2.1

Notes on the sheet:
MCU Decoupling
Reset conditioning
VCore filter
Current amp: UCB0 debug UART: UCA0 CAN_BUS: UCA1
Digi-Pot -------------------------------- I2C Address 0x01 Dual channel pot used to adjust output voltage on two channels
Low power buck-boost rail -------------------------------- 1A max adjustible votage rail output voltage adjusted through digi-pot
3.3V Rail -------------------------------- 1A max output Uses comparator to disable the rail when voltage drops below cutoff for battery type
V bus -------------------------------- High Amperage linear regulator Can be bypassed, allowing unregulated battery voltage on line
Current sense amplifier ------------------------------------------ I2C address: 10000000
Cutoff Voltage selection ----------------------------------------- 0 0 : LiPo (3.2 V cutoff) 0 1 : NiMH (2V cutoff) 1 x : Default (1.1V)
